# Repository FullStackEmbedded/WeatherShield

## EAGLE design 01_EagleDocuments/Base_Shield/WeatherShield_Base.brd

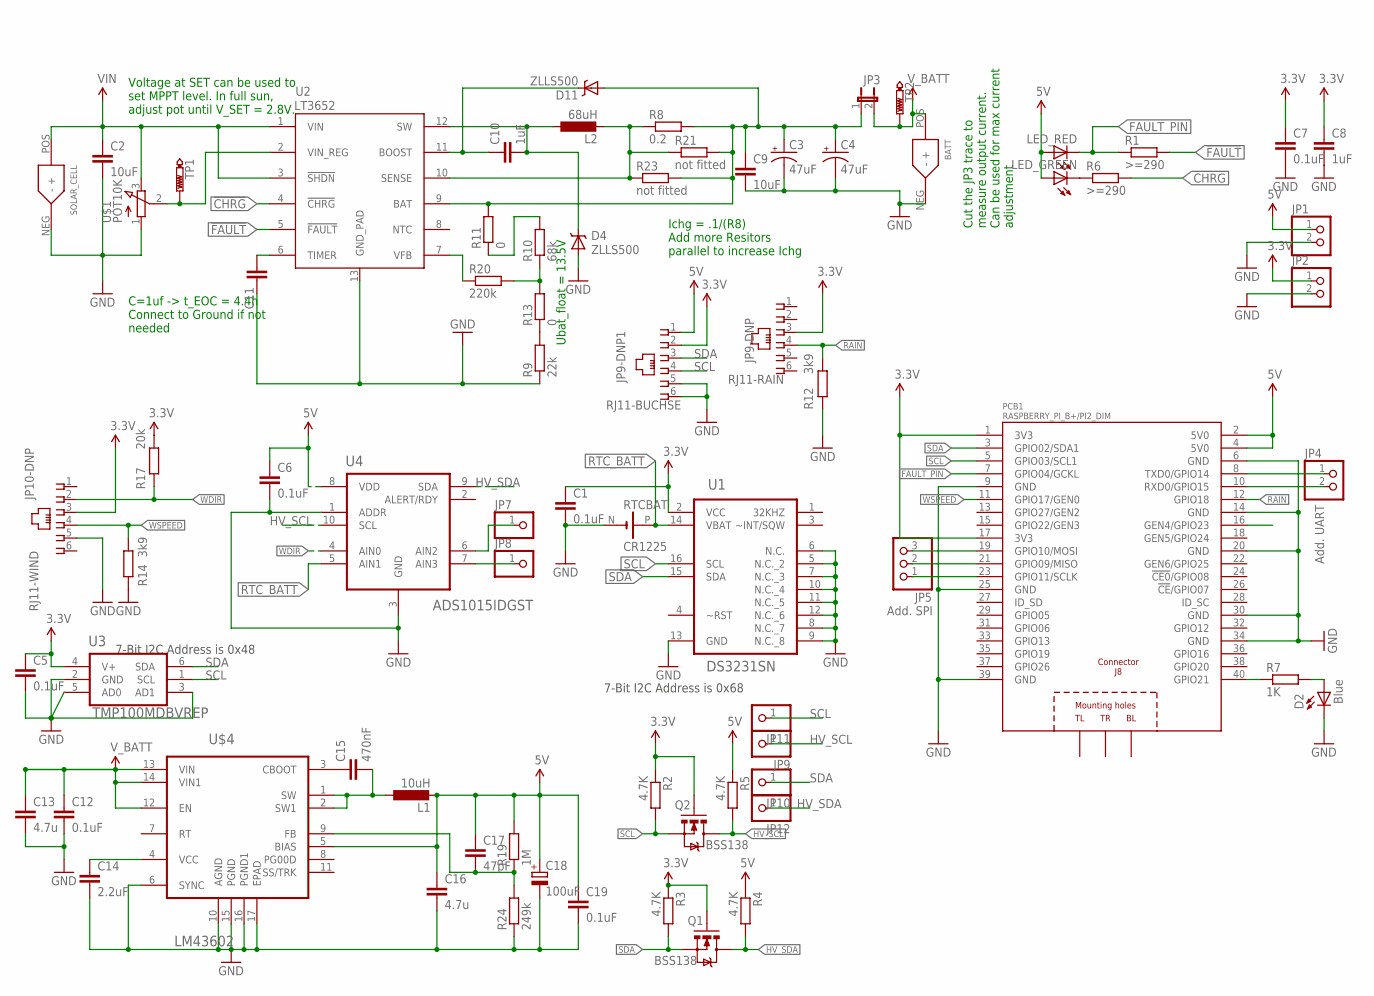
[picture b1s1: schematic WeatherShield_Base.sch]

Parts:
BATT: XT-60
C1, C5, C6, C7: 0.1uF; C0603
C2, C9: 10uF; C0603
C3, C4: 47uF; EIA7343-20
C8, C10: 1uF; C0603
C11: 1.0uF; C0603
C12, C19: 0.1uF; C1206
C13: 4.7u; C1206
C14: 2.2uF; C0603
C15: 470nF; C0603
C16: 4.7u; C0603
C17: 47pF; C0603
C18: 100uF; E2,5-6E
D2: Blue; LED-0603
D4, D11: ZLLS500; SOT23
JP1, JP2, JP4: PINHD-1X2; 1X02
JP3: JUMPER-PTH-2-NC; PTH-JUMPER-NC_BOTTOM_NO_SILK
JP5: PINHD-1X3; 1X03
JP7, JP8, JP9, JP10, JP11, JP12: PINHD-1X1; 1X01
JP9-DNP: RJ11-RAIN; RJ11-STECKER
JP9-DNP1: RJ11-BUCHSE; RJ11-STECKER
JP10-DNP: RJ11-WIND; RJ11-STECKER
L1: 10uH; 6000-XXXX-RC
L2: 68uH; 6000-XXXX-RC
LED_GREEN: LEDSML0603; SML0603
LED_RED: LEDSML0603; SML0603
PCB1: RASPBERRY_PI_B+/PI2_DIM; RASPBERRY_PI_BPLUS_DIM
Q1, Q2: BSS138; SOT23-3
R1, R6: >=290; R0603
R2, R3, R4, R5: 4.7K; R0603
R7: 1K; R0603
R8: 0.2; R0805
R9: 22k; R0603
R10: 68k; R0603
R11, R13: 0; R0603
R12, R14: 3k9; R0603
R17: 20k; R0603
R19: 1M; R0805
R20: 220k; R0603
R21, R23: not fitted; R0805
R24: 249k; R0805
RTCBAT: CR1225; BATTERIE_HALTER_CR1225
SOLAR_CELL: XT-60
TP1, TP2: SET; B1,27
U1: DS3231SN; SOIC127P1032X265-16N
U2: LT3652; MSOP-12_GND
U3: TMP100MDBVREP; SOT95P280X145-6N
U4: ADS1015IDGST; SOP50P490X110-10N
U$1: POT10K; POT_TS63Y_10K
U$4: LM43602; HTSSOP-16

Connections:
3.3V: C1.1, C5.1, C7.1, C8.1, JP2.1, JP9-DNP.3, JP9-DNP1.2, JP10-DNP.3, PCB1.1 (3V3), PCB1.17 (3V3), Q1.1 (G), Q2.1 (G), R2.1, R3.1, R17.1, U1.2 (VCC), U3.4 (V+)
5V: C6.1, C16.1, C17.1, C18.+, C19.1, JP1.1, JP9-DNP1.1, L1.2, LED_GREEN.A, LED_RED.A, PCB1.2 (5V0), PCB1.4 (5V0), R4.1, R5.1, R19.2, U4.8 (VDD), U$4.5 (BIAS)
!CHRG: R6.2, U2.4 (!CHRG)
!FAULT: R1.2, U2.5 (!FAULT)
BOOST: C10.1, D11.3 (C), U2.11 (BOOST)
FAULT_PIN: LED_RED.C, PCB1.7 (GPIO04/GCKL), R1.1
FB: R10.1, R13.2, R20.2
HV_SCL: JP9.1, Q2.3 (D), R5.2, U4.10 (SCL)
HV_SDA: JP12.1, Q1.3 (D), R4.2, U4.9 (SDA)
unnamed: R9.2, R13.1
unnamed: R10.2, R11.1
unnamed: LED_GREEN.C, R6.1
unnamed: JP7.1, U4.6 (AIN2)
unnamed: JP8.1, U4.7 (AIN3)
unnamed: D2.A, R7.2
unnamed: R20.1, U2.7 (VFB)
unnamed: C3.A (+), C4.A (+), C9.1, D11.1 (A), JP3.1, R8.2, R11.2, R21.2, R23.2, U2.9 (BAT)
unnamed: C15.1, U$4.3 (CBOOT)
unnamed: JP4.1, PCB1.8 (TXD0/GPIO14)
unnamed: JP4.2, PCB1.10 (RXD0/GPIO15)
unnamed: JP5.3, PCB1.19 (GPIO10/MOSI)
unnamed: JP5.2, PCB1.21 (GPIO09/MISO)
unnamed: C17.2, R19.1, R24.2, U$4.9 (FB)
unnamed: C14.1, U$4.4 (VCC)
unnamed: C15.2, L1.1, U$4.1 (SW), U$4.2 (SW1)
unnamed: JP5.1, PCB1.23 (GPIO11/SCLK)
RAIN: JP9-DNP.4, PCB1.12 (GPIO18), R12.1
RTC_BATT: RTCBAT.P (+), U1.14 (VBAT), U4.5 (AIN1)
SCL: JP9-DNP1.4, JP11.1, PCB1.5 (GPIO03/SCL1), Q2.2 (S), R2.2, U1.16 (SCL), U3.1 (SCL)
SDA: JP9-DNP1.3, JP10.1, PCB1.3 (GPIO02/SDA1), Q1.2 (S), R3.2, U1.15 (SDA), U3.6 (SDA)
SENSE: L2.2, R8.1, R21.1, R23.1, U2.10 (SENSE)
SET: TP1.TP, U2.2 (VIN_REG), U$1.2 (S)
STAT3: PCB1.40 (GPIO21), R7.1
SW: C10.2, D4.3 (C), L2.1, U2.12 (SW)
TIMER: C11.2, U2.6 (TIMER)
VIN: C2.1, SOLAR_CELL.POS (+), U2.1 (VIN), U2.3 (!SHDN), U$1.3 (E)
V_BATT: BATT.POS (+), C12.1, C13.1, JP3.2, TP2.TP, U$4.12 (EN), U$4.13 (VIN), U$4.14 (VIN1)
WDIR: JP10-DNP.2, R17.2, U4.4 (AIN0)
WSPEED: JP10-DNP.4, PCB1.11 (GPIO17/GEN0), R14.1

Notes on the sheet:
Cut the JP3 trace to measure output current. Can be used for max current adjustment
Ichg = .1/(R8) Add more Resitors parallel to increase Ichg
Voltage at SET can be used to set MPPT level. In full sun, adjust pot until V_SET = 2.8V.
C=1uf -> t_EOC = 4.4h Connect to Ground if not needed
Add. UART
Add. SPI
7-Bit I2C Address is 0x68
7-Bit I2C Address is 0x48
Ubat_float = 13.5V

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
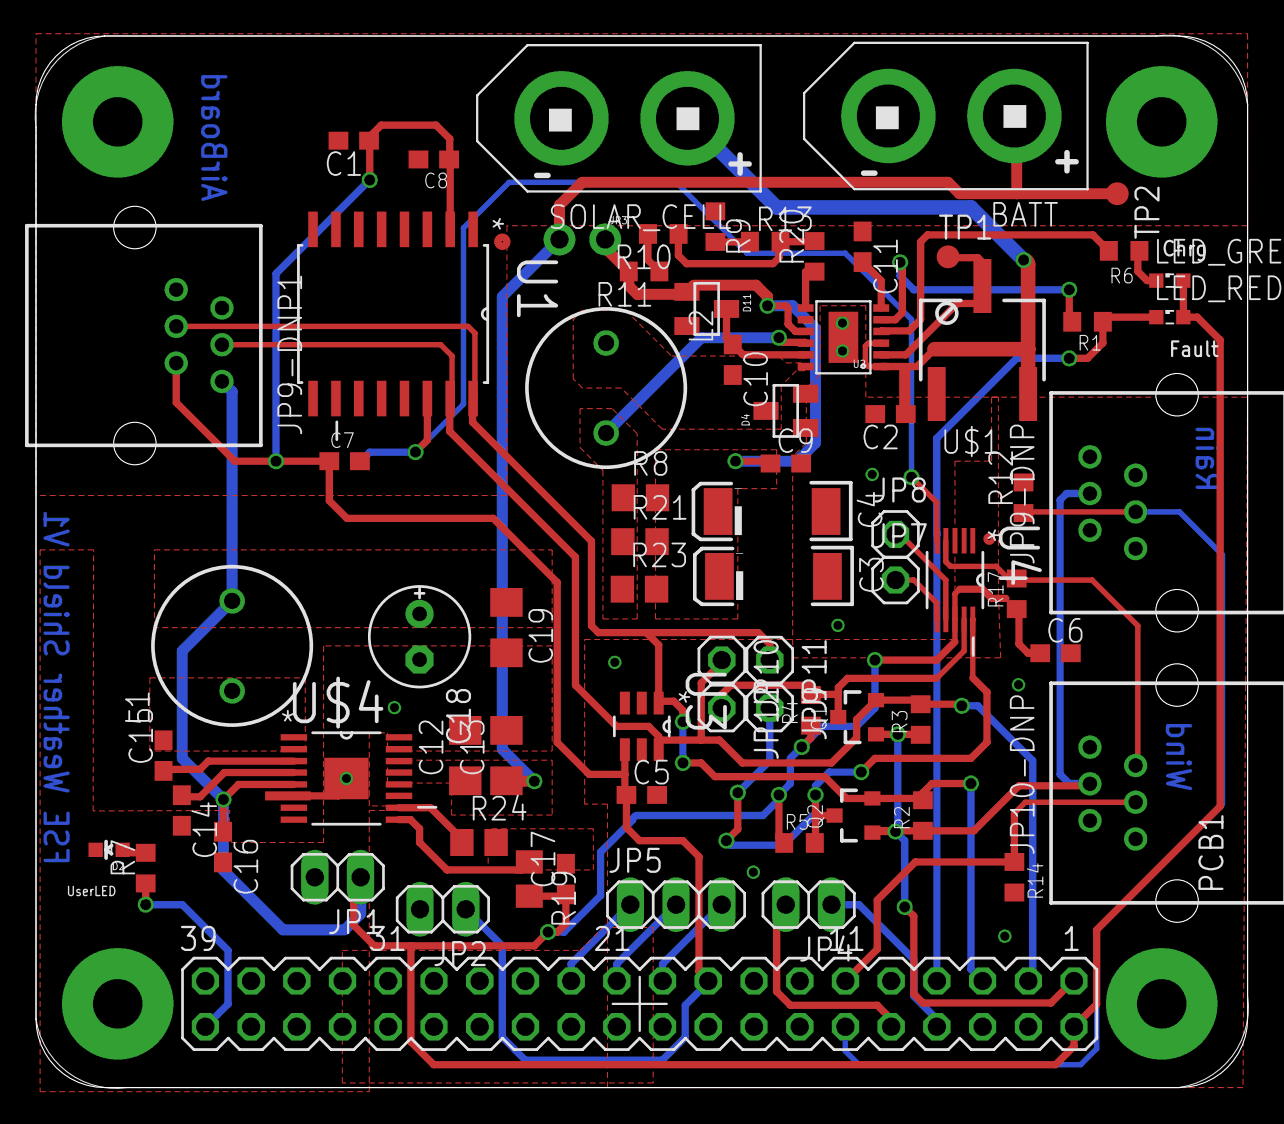
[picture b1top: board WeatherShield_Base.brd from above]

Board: 2 copper layers, 67.3 x 58.4 mm, 74 parts (1 on the bottom side), 40 nets.

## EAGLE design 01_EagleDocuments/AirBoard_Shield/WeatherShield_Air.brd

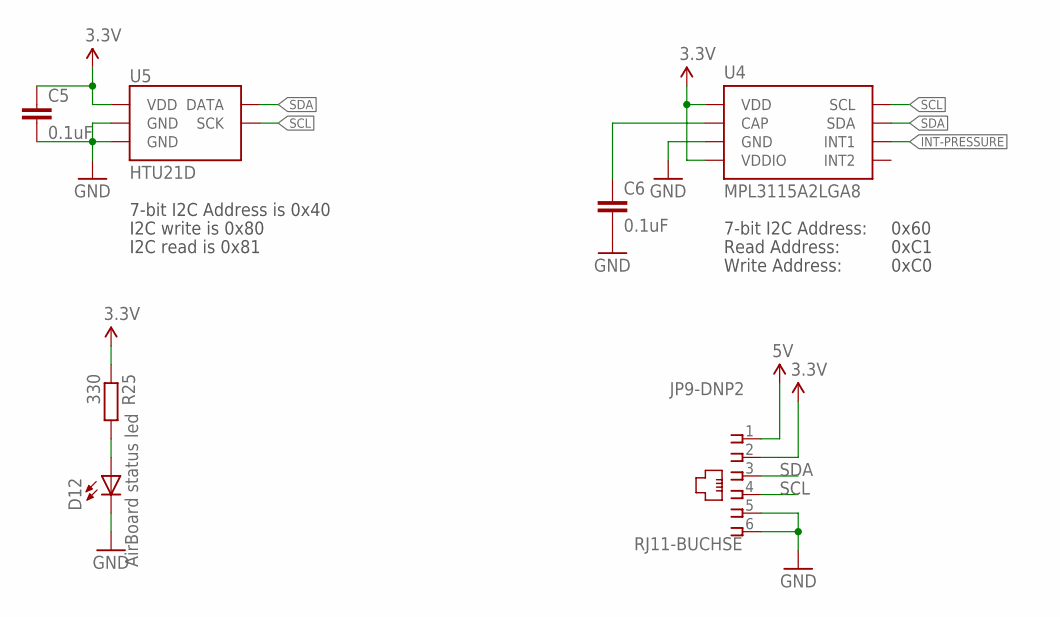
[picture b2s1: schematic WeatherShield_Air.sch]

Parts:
C5, C6: 0.1uF; C0603
D12: AirBoard status led; LED-0603
JP9-DNP2: RJ11-BUCHSE; RJ11-STECKER
R25: 330; R0603
U4: MPL3115A2LGA8; LGA8
U5: HTU21D

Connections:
3.3V: C5.1, JP9-DNP2.2, R25.1, U4.1 (VDD), U4.4 (VDDIO), U5.VDD
5V: JP9-DNP2.1
GND: C5.2, C6.2, D12.C, JP9-DNP2.5, JP9-DNP2.6, U4.3 (GND), U5.7 (GND), U5.GND
INT-PRESSURE: U4.6 (INT1)
unnamed: C6.1, U4.2 (CAP)
unnamed: D12.A, R25.2
SCL: JP9-DNP2.4, U4.8 (SCL), U5.SCK
SDA: JP9-DNP2.3, U4.7 (SDA), U5.DATA

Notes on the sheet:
Read Address:
Write Address:
7-bit I2C Address:
0x60
0xC1
0xC0
7-bit I2C Address is 0x40
I2C write is 0x80
I2C read is 0x81

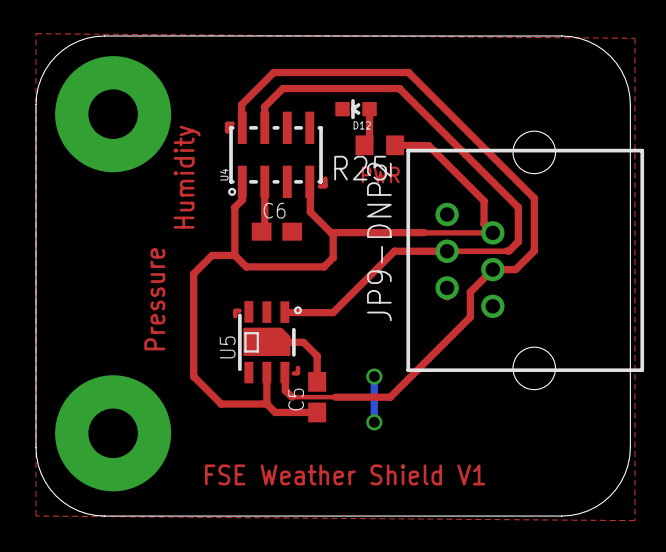
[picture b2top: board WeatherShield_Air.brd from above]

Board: 2 copper layers, 33.0 x 26.7 mm, 7 parts (0 on the bottom side), 6 nets.

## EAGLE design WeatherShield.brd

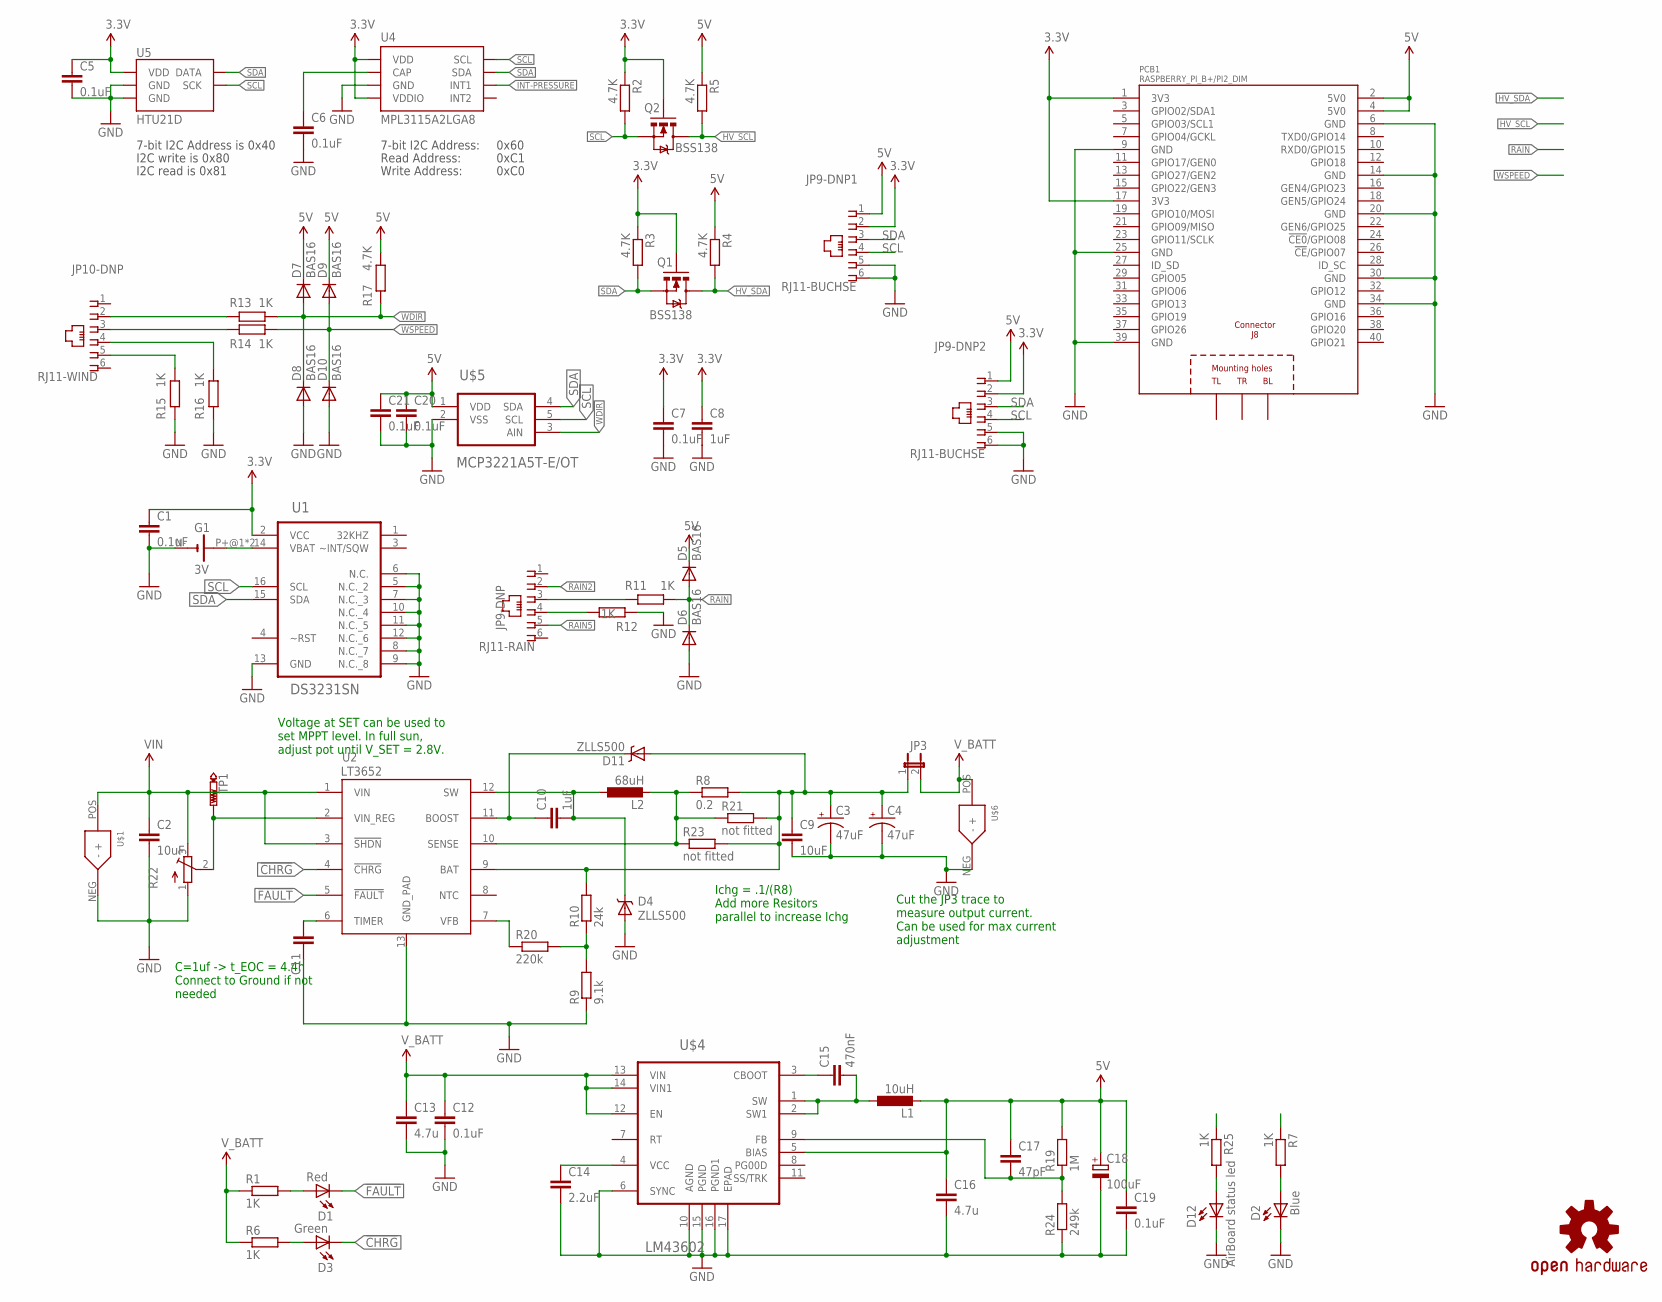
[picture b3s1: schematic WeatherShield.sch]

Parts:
C1, C5, C6, C7, C20, C21: 0.1uF; C0603
C2, C9: 10uF; C0603
C3, C4: 47uF; EIA7343-20
C8, C10: 1uF; C0603
C11: 1.0uF; C0603
C12, C19: 0.1uF; C1206
C13: 4.7u; C1206
C14: 2.2uF; C0603
C15: 470nF; C0603
C16: 4.7u; C0603
C17: 47pF; C0603
C18: 100uF; E2,5-6E
D1: Red; LED-0603
D2: Blue; LED-0603
D3: Green; LED-0603
D4, D11: ZLLS500; SOT23
D5, D6, D7, D8, D9, D10: BAS16; SOD-323
D12: AirBoard status led; LED-0603
G1: 3V; CELL_RETAINER_11.6MM
JP3: JUMPER-PTH-2-NC; PTH-JUMPER-NC_BOTTOM_NO_SILK
JP9-DNP: RJ11-RAIN; RJ11-STECKER
JP9-DNP1, JP9-DNP2: RJ11-BUCHSE; RJ11-STECKER
JP10-DNP: RJ11-WIND; RJ11-STECKER
L1: 10uH; 6000-XXXX-RC
L2: 68uH; 6000-XXXX-RC
LOGO1: OSHW-LOGOM; OSHW-LOGO-M
PCB1: RASPBERRY_PI_B+/PI2_DIM; RASPBERRY_PI_BPLUS_DIM
Q1, Q2: BSS138; SOT23-3
R1, R6, R7, R11, R12, R13, R14, R15, R16, R25: 1K; R0603
R2, R3, R4, R5, R17: 4.7K; R0603
R8: 0.2; R0805
R9: 9.1k; R0603
R10: 24k; R0603
R19: 1M; R0805
R20: 220k; R0603
R21, R23: not fitted; R0805
R22: TRIM_EU-SM-42/43A; SM-42/43A
R24: 249k; R0805
TP1: SET; B1,27
U1: DS3231SN; SOIC127P1032X265-16N
U2: LT3652; MSOP-12_GND
U4: MPL3115A2LGA8; LGA8
U5: HTU21D
U$1, U$6: XT-60
U$4: LM43602; HTSSOP-16
U$5: MCP3221A5T-E/OT; SOT95P270X145-5N

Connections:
3.3V: C1.1, C5.1, C7.1, C8.1, JP9-DNP1.2, JP9-DNP2.2, PCB1.1 (3V3), PCB1.17 (3V3), Q1.1 (G), Q2.1 (G), R2.1, R3.1, U1.2 (VCC), U4.1 (VDD), U4.4 (VDDIO), U5.VDD
5V: C16.1, C17.1, C18.+, C19.1, C20.1, C21.1, D5.1 (C), D7.1 (C), D9.1 (C), JP9-DNP1.1, JP9-DNP2.1, L1.2, PCB1.2 (5V0), PCB1.4 (5V0), R4.1, R5.1, R17.1, R19.2, U$4.5 (BIAS), U$5.1 (VDD)
!CHRG: D3.C, U2.4 (!CHRG)
!FAULT: D1.C, U2.5 (!FAULT)
BOOST: C10.1, D11.3 (C), U2.11 (BOOST)
FB: R9.2, R10.1, R20.2
GND: C1.2, C2.2, C3.C (-), C4.C (-), C5.2, C6.2, C7.2, C8.2, C9.2, C11.1, C12.2, C13.2, C14.2, C16.2, C18.-, C19.2, C20.2, C21.2, D2.C, D4.1 (A), D6.2 (A), D8.2 (A), D10.2 (A), D12.C, G1.N- (-), JP9-DNP1.5, JP9-DNP1.6, JP9-DNP2.5, JP9-DNP2.6, PCB1.6 (GND), PCB1.9 (GND), PCB1.14 (GND), PCB1.20 (GND), PCB1.25 (GND), PCB1.30 (GND), PCB1.34 (GND), PCB1.39 (GND), R9.1, R12.2, R15.2, R16.2, R22.1 (A), R24.1, U1.5 (N.C._2), U1.6 (N.C.), U1.7 (N.C._3), U1.8 (N.C._7), U1.9 (N.C._8), U1.10 (N.C._4), U1.11 (N.C._5), U1.12 (N.C._6), U1.13 (GND), U2.13 (GND_PAD), U4.3 (GND), U5.7 (GND), U5.GND, U$1.NEG (-), U$4.6 (SYNC), U$4.10 (AGND), U$4.15 (PGND), U$4.16 (PGND1), U$4.17 (EPAD), U$5.2 (VSS), U$6.NEG (-)
HV_SCL: Q2.3 (D), R5.2
HV_SDA: Q1.3 (D), R4.2
INT-PRESSURE: U4.6 (INT1)
unnamed: JP10-DNP.3, R14.2
unnamed: JP10-DNP.2, R13.2
unnamed: D1.A, R1.2
unnamed: JP9-DNP.3, R11.2
unnamed: C6.1, U4.2 (CAP)
unnamed: G1.P+@1 (+), G1.P+@2 (+), U1.14 (VBAT)
unnamed: D3.A, R6.2
unnamed: D2.A, R7.2
unnamed: JP9-DNP.4, R12.1
unnamed: JP10-DNP.5, R15.1
unnamed: JP10-DNP.4, R16.1
unnamed: R20.1, U2.7 (VFB)
unnamed: C3.A (+), C4.A (+), C9.1, D11.1 (A), JP3.1, R8.2, R10.2, R21.2, R23.2, U2.9 (BAT)
unnamed: C15.1, U$4.3 (CBOOT)
unnamed: C17.2, R19.1, R24.2, U$4.9 (FB)
unnamed: C14.1, U$4.4 (VCC)
unnamed: C15.2, L1.1, U$4.1 (SW), U$4.2 (SW1)
unnamed: D12.A, R25.2
RAIN: D5.2 (A), D6.1 (C), R11.1
RAIN2: JP9-DNP.2
RAIN5: JP9-DNP.5
SCL: JP9-DNP1.4, JP9-DNP2.4, Q2.2 (S), R2.2, U1.16 (SCL), U4.8 (SCL), U5.SCK, U$5.5 (SCL)
SDA: JP9-DNP1.3, JP9-DNP2.3, Q1.2 (S), R3.2, U1.15 (SDA), U4.7 (SDA), U5.DATA, U$5.4 (SDA)
SENSE: L2.2, R8.1, R21.1, R23.1, U2.10 (SENSE)
SET: R22.2 (S), TP1.TP, U2.2 (VIN_REG)
STAT1: R25.1
STAT3: R7.1
SW: C10.2, D4.3 (C), L2.1, U2.12 (SW)
TIMER: C11.2, U2.6 (TIMER)
VIN: C2.1, R22.3 (E), U2.1 (VIN), U2.3 (!SHDN), U$1.POS (+)
V_BATT: C12.1, C13.1, JP3.2, R1.1, R6.1, U$4.12 (EN), U$4.13 (VIN), U$4.14 (VIN1), U$6.POS (+)
WDIR: D7.2 (A), D8.1 (C), R13.1, R17.2, U$5.3 (AIN)
WSPEED: D9.2 (A), D10.1 (C), R14.1

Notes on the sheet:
Read Address:
Write Address:
7-bit I2C Address:
0x60
0xC1
0xC0
7-bit I2C Address is 0x40
I2C write is 0x80
I2C read is 0x81
Cut the JP3 trace to measure output current. Can be used for max current adjustment
Ichg = .1/(R8) Add more Resitors parallel to increase Ichg
Voltage at SET can be used to set MPPT level. In full sun, adjust pot until V_SET = 2.8V.
C=1uf -> t_EOC = 4.4h Connect to Ground if not needed

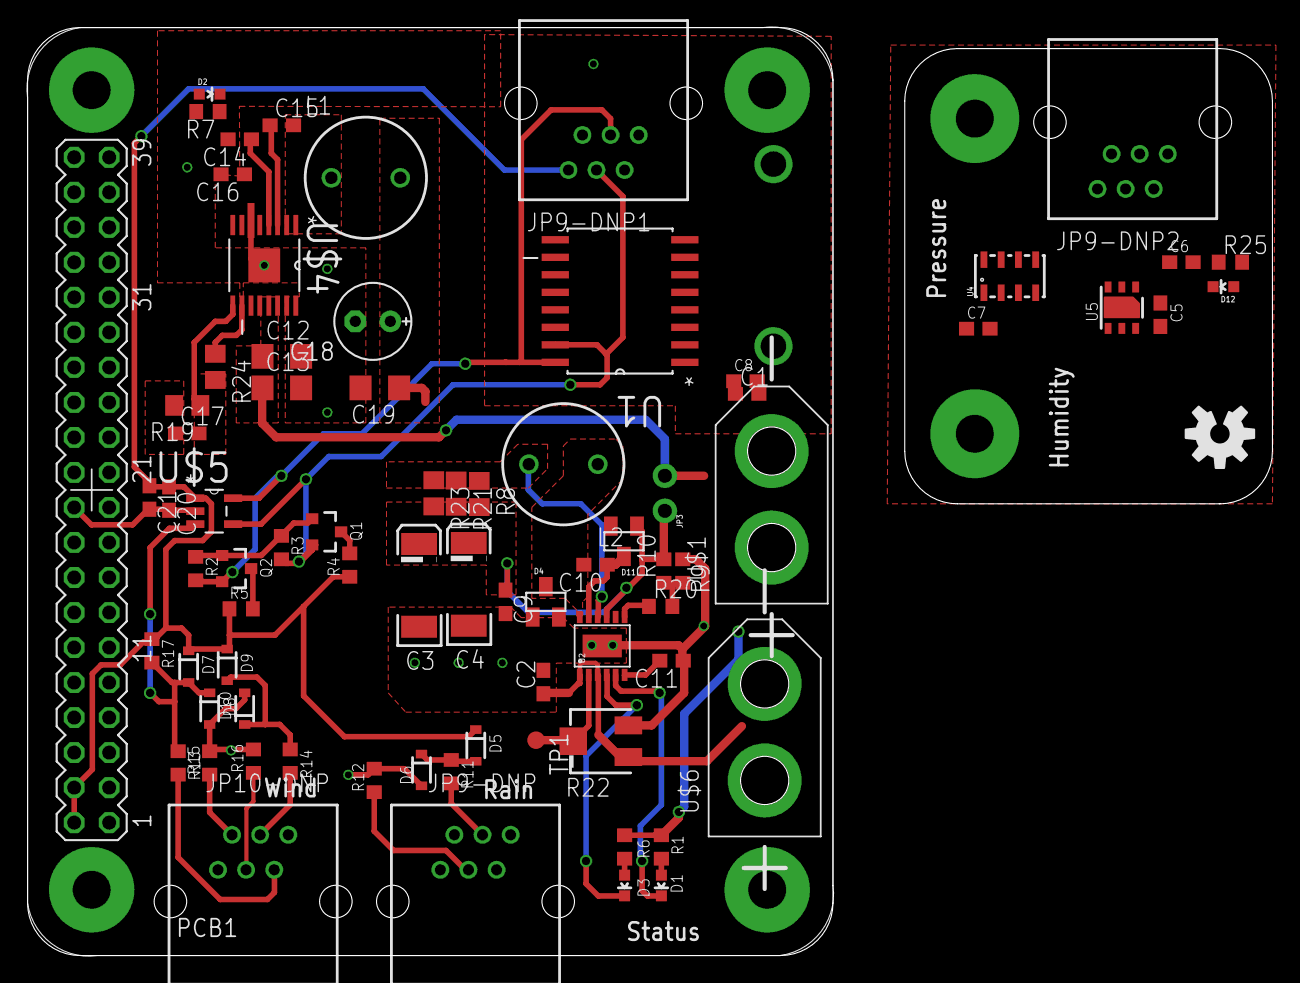
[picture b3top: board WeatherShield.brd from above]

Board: 2 copper layers, 90.3 x 67.3 mm, 78 parts (1 on the bottom side), 38 nets.

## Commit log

2015-07-08 FSE_Weather_Shield.lbr added
2015-07-14 routing...
2015-07-15 initial project version
2015-07-19 Solar Panel routing done
2015-07-20 Files rename
2015-07-20 Power parts
2015-07-23 5V supply done
2015-07-23 cleaning up
2015-07-23 EagleCleanup.py added
2015-07-24 routing
2015-07-26 WeatherShield_v1
2015-07-27 WeatherShield v1
    Restructuration des Fichiers
    Division en Air et Base Board
2015-07-27 WeatherShield v1
    First attempt almost done
    GPIO routing is missing
2015-07-27 WeatherShield v1
2015-07-31 WeatherShield_v1
    routing....
2015-08-04 Add LICENSE
2015-09-14 WeatherShield_v1
    Documentation added
2015-10-09 Reorganize driver classes
2015-10-09 Implement prototypical scheduler
2015-11-12 Implement scheduler for real application
    Sensor polling is performed by separate threads dispatched in the main
    function. Polling intervals, etc. are still hardwired.

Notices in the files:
parts and their libraries:
SparkFun-Sensors: Licensing: CC v3.0 Share-Alike You are welcome to use this library for commercial purposes.
